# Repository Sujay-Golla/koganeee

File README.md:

# Koganeee 
(JJK Reference) Flying room voice assistant with a screen  

**Demo video:** https://youtu.be/gkjLtGN1tb8

## Inspiration
As a Jujutsu Kaisen fan and an admirer of flying pets, I wanted to make Kogane for my room. The objective of Kogane is to be a person-following flying pet assistant that can communicate with voice and through a retractable screen, sort of like a flying Alexa but friendlier! I also wanted to make drones for a while and it seemed like a cool approach to make Kogane. A use case that I had in mind is when I'm working in my room and my hands are busy and if I need to quickly pull up a tutorial, I would normally have to put things down to find my laptop. Instead with Kogane, I can call for Kogane wherever I am in my room and quickly check for information or pull up a Youtube tutorial from its screen without any physical contact. 

## Challenges
I was new to building FCs and drones, so I had to spend a lot of time getting advice from my friends and revising designs. The timeline was also a bit tight as I had to finish it by Open Sauce. There were a lot of errors on the PCB that I had not anticipated, so I had to make a lot of tweaks with soldering. I also made expensive mistakes with batteries and ESCs but eventually made it work.  

## Technical Features
In terms of the technical features, it is a drone that can be radio controlled, but ready to be implemented with a room-based camera-mmWave sensor fused navigation system for object and person detection, currently displayed in a dashboard for demo. Koganeee also has a mic and LCD screen for the built-in voice assistant with a live Weather app and a Tasks app. It hosts 1303 Brushless motors, a big 1100mAH 4S LiPo battery, and a custom FC with STM32F722RET6 and ESP32-S3-WROOM. Flight computation with accelerometer and ToF sensor is done on-board with the STM32, and is complemented by the ESP32 for data transmission, whether it be directions for autonomous tracking or for cards to be displayed on the screen. 

## Guide to recreating your very own Koganeee!

1. **Start with a revised BOM:** Start off with my [BOM.csv](BOM.csv), check connector compatibility for different modules, and make a good plan for making reliable harnesses
2. **3D Print your Koganeee:** The [CAD folder](cad/) contains the assembly for the shell and drone design, feel free to change the frame type and revise the shell as needed, taking into account some of the notes I added under [CAD notes](cad/README.md) regarding shell assembly, total weight and propeller-clearance.
3. **The flight controller:** Review the [PCB notes](pcb/README.md) and make adjustments to the PCB before ordering it, it's definitely also possible to make it more compact with smaller connectors and better planning, so plan for space optimization!
4. **Set up the firmware.** Follow the [firmware guide](firmware/README.md) for the toolchains and setup order, most of the details for the firmware setup as well as the firmware files are already available and can easily be modified! 
5. **Test in stages:** The [demo guides](firmware/Demo/INDEX.md) cover voice commands, the LCD, microphone, weather, tasks and room mapping, so check those out and ask your favorite AI (I prefer Sol or Gemini) for any clarifications
6. **Go through tests for a safe flight:** Follow the [flight preparation guide](firmware/Demo/FIRST_FLIGHT_PLAN.md), verifying the orientation, radio control and failsafe with propellers off, and as well as the physical connections, especially harnesses and soldered joints

## Build

## CAD Model
### Kogane

### Internal Drone

## PCB
### Fabricated PCB

### Schematic

### PCB Design

### 3D Model

## BOM

| Item | Qty | Price (USD) | Link | Notes |
|------|-----|-------------|------|-------|
| 1303 5500KV brushless motor | 4 | $67.61 | [Rotor Village](https://rotorvillage.ca/geprc-speedx2-1303-5-5500kv-motor/) | |
| 3-inch Gemfan 3018 2-Blade Propeller (4 pairs) | 1 | $3.94 | [AliExpress](https://www.aliexpress.com/item/1005007476443932.html) | |
| 4-in-1 ESC 45A 20x20 | 1 | $30.55 | [AliExpress](https://www.aliexpress.com/item/1005009278492069.html) | |
| GNB 1100mAh 4S 120C HV LiPo XT60 | 1 | $19.72 | [Rotor Village](https://rotorvillage.ca/gnb-1100mah-4s-120c-hv-lipo-xt60/) | |
| Battery strap | 1 | $3.88 | [AliExpress](https://www.aliexpress.com/item/4001316238579.html) | |
| Custom Kogane FC PCB | 2 | $168.84 | [JLCPCB](https://jlcpcb.com) | Design submitted but revisions noted under in the PCB directory (min 2 assembled PCBs) |
| ESP32-S3-WROOM-1-N16R8 | 1 | $15.79 | [AliExpress](https://www.aliexpress.com/item/1005012502278371.html) | Manual solder |
| VL53L1X ToF sensor | 1 | $4.83 | [AliExpress](https://www.aliexpress.com/item/1005007324288727.html) | Manual solder |
| 8GB microSD card | 1 | $3.49 | [AliExpress](https://www.aliexpress.com/item/1005010323860143.html) | FAT32 for iNAV blackbox |
| OV2640 FPC camera module 75MM-160 650nm | 1 | $9.19 | [AliExpress](https://www.aliexpress.com/item/1005003040149873.html) | |
| ILI9341 2.8 inch SPI touch display | 1 | $5.69 | [AliExpress](https://www.aliexpress.com/item/1005006315533240.html) | |
| INMP441 I2S microphone | 1 | $1.59 | [AliExpress](https://www.aliexpress.com/item/1005009213592784.html) | |
| 4 ohm 3W speaker | 1 | $2.46 | [AliExpress](https://www.aliexpress.com/item/1005008626624201.html) | |
| MG90S micro servo | 0 | $0.00 | | Already owned |
| HLK-LD2450 mmWave module | 1 | $6.69 | [AliExpress](https://www.aliexpress.com/item/1005010228798692.html) | |
| USB-UART adapter 3.3V logic | 1 | $1.77 | [AliExpress](https://www.aliexpress.com/item/1005006445462581.html) | Powers LD2450 from laptop USB |
| USB webcam 720p or 1080p | 2 | $7.95 | [AliExpress](https://www.aliexpress.com/item/1005007740023631.html) | Fixed position to laptop USB |
| 4S LiPo charger with AC plug | 1 | $15.00 | [Amazon](https://www.amazon.ca/dp/B0B3Y3JGDG) | |
| XT60 Pigtail Male | 1 | $1.48 | [AliExpress](https://www.aliexpress.com/item/1005009156026988.html) | |
| Radio TX module | 1 | $4.23 | [AliExpress](https://www.aliexpress.com/item/1005010228737836.html) | For future integration as RC transmitter is currently out of budget |
| JST Connector kit | 1 | $6.09 | [AliExpress](https://www.aliexpress.com/item/1005010491522001.html) | |
| M2 nylon standoff kit | 1 | $3.68 | [AliExpress](https://www.aliexpress.com/item/32862529967.html) | |
| Filament (PLA for shell and PETG GF for drone frame) | 2 | $28.68 | [Amazon](https://a.co/d/04z5qBoh) [Amazon](https://a.co/d/00EyYI3x) | doesn't require that much filament, so smaller spools is okay! |
| Connectors, adapters, USB extensions | Depends | < $30 | AliExpress | |
| Radiomaster Pocket | 1 | $96.51 | [Amazon](https://www.amazon.ca/Radiomaster-Transmitter-Portable-Charcoal-transmitter/dp/B0GWPZ96C5?source=ps-sl-shoppingads-lpcontext&th=1) | Or borrow from a friend like I did for testing |

**Total cost (upper bound): $539.66**

## Credits
https://macondo.hackclub.com/docs/flight-controller#stm32cubemx - Very useful guide :D
Thanks to Surya and Alvik for all their guidance with the PCB, drone design, and throughout the build!
Used ChatGPT and various Claude models throughout the design and build process. Only used them for documentation for draft and format generation, I've looked through and edited all of them to keep them consistent with my understanding of the project, so that it is more readable for other people trying to recreate it.

## Next Steps
While all the firmware is available, I didn't have time to install and calibrate cameras for full autonomy. Also didn't have time to design a proper mechanism for screen retraction but that could a simple pulley driven by one servo.

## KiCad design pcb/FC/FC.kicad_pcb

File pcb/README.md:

# PCB notes

The flight-controller source is in [FC/](FC/). The physical prototypes include hand repairs that are absent from these files.

## Fixes for the next revision

| Issue | Fix |
| --- | --- |
| R22 pulls ESP32 IO0 down and SW3 drives it high. | Add a 10 kΩ pull-up and a BOOT button to GND. The original circuit required SW3 for normal boot. The working prototype was repaired. |
| ESP32 EN floats and is connected to STM32 PB4. | Add a dedicated pull-up and reset timing. Design any STM32 reset control explicitly. |
| ESP32 native USB is not routed. | Route GPIO19/20 to a connector with ESD protection. |
| U11 speaker amplifier has SD_MODE tied to GND. | Correct the enable and channel-selection circuit. Do not connect the grounded pin directly to 3.3 V. |
| Battery ADC PC0 is unconnected. | Add a scaled, filtered divider and an accessible test point. |
| F1 is specified for 16 V and Q2 can exceed its ±8 V VGS rating. | Review the power path for full 4S/LiHV voltage, transients and USB backfeeding. |
| Connectors do not match some purchased modules. | Choose exact mating parts, label pin 1 and add strain relief and repair access. |
| LCD and camera reset share the STM32 reset net. LCD MISO is absent. | Add independent peripheral reset and route readback if required. |
| Some labels and firmware assumptions are stale. | Reconcile I2S directions, UARTs, the 25 MHz clock and motor timer/DMA assignments. Reserve the N16R8 memory pins. |

## Before ordering

- Reconcile BOM values and supplier IDs with the chosen components.
- Regenerate ERC and DRC. The saved report is historical.
- Verify the complete ESC harness pinout and every connector's orientation.
- Add test points for supply rails, reset, boot, UART and ADC signals.
- Check power selection and intended loads on the assembled revision.

Details are in the [firmware guide](../firmware/README.md), [pin map](../firmware/companion-esp32s3/PINMAP.md), [power review](../firmware/fc-inav/POWER_REVIEW.md) and [battery-sensing notes](../firmware/fc-inav/BATTERY_SENSE_CHECK.md).

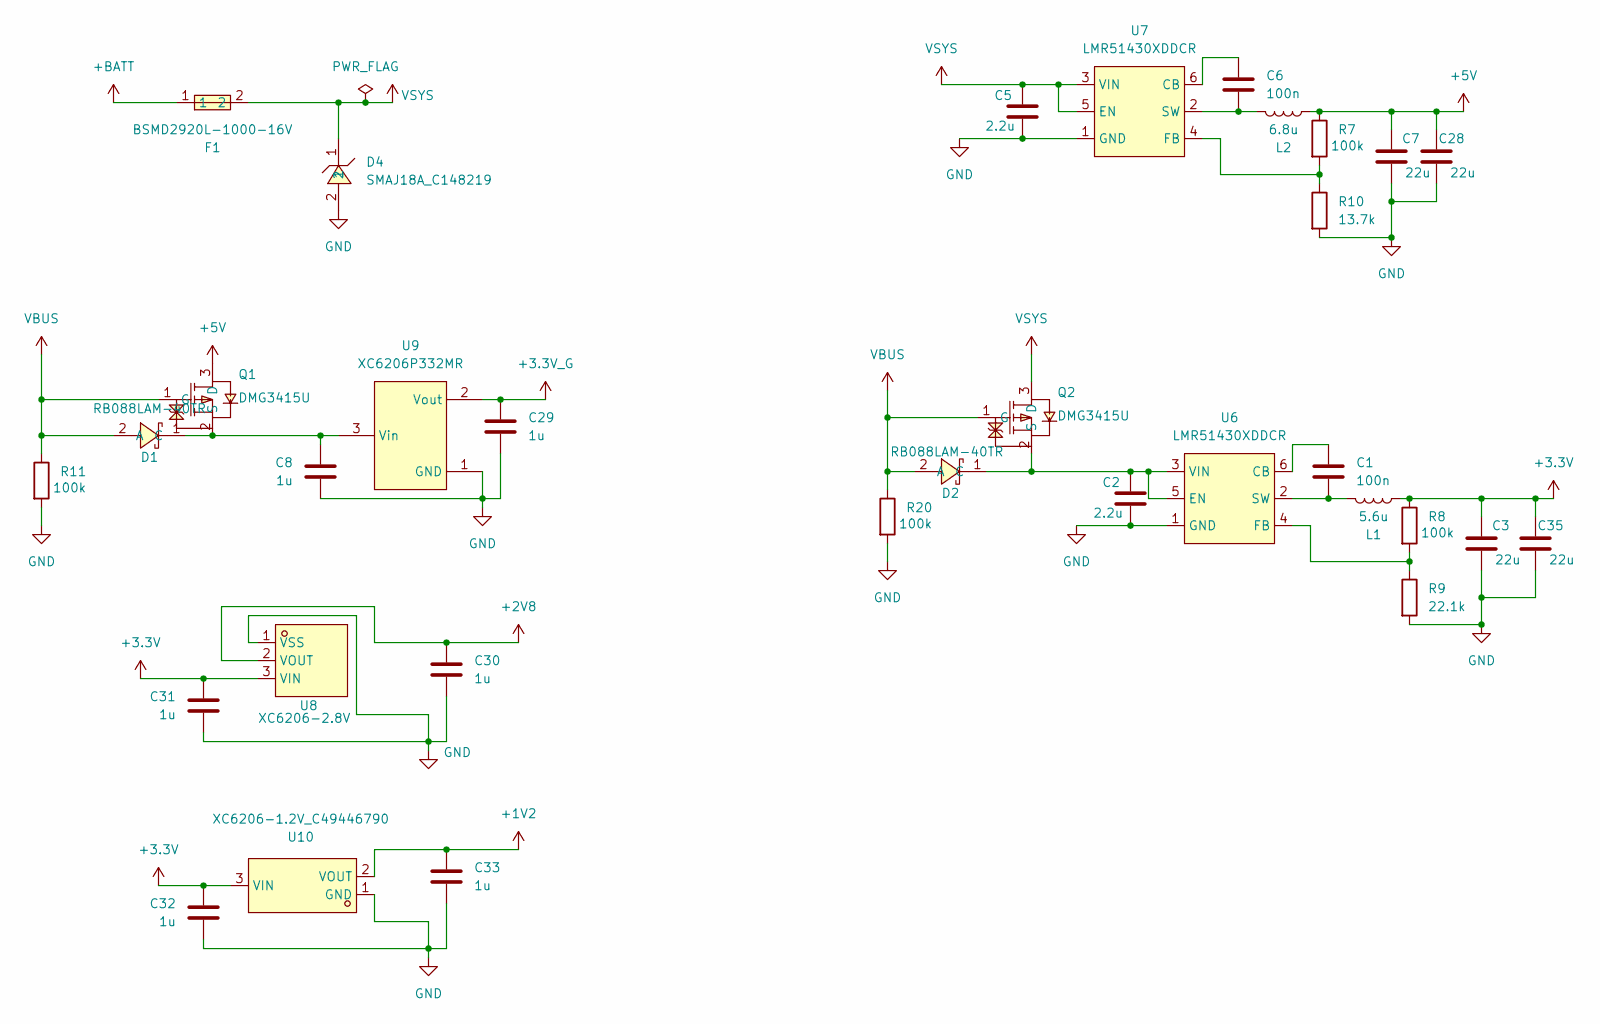
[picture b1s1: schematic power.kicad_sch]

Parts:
C1, C6: 100n; C0603
C2, C5: 2.2u; C0603
C3, C7, C28, C35: 22u; C0805
C8, C29, C30, C31, C32, C33: 1u; C0603
D1, D2: RB088LAM-40TR; SOD-128_L3.7-W2.5-LS4.7-RD; MPN RB088LAM-40TR; LCSC Part C3758383
D4: SMAJ18A_C148219; SMA_L4.4-W2.6-LS5.0-RD; MPN SMAJ18A; LCSC Part C148219
F1: BSMD2920L-1000-16V; F2920; MPN BSMD2920L-1000-16V; LCSC Part C46597958
L1: 5.6u; IND-SMD_L7.0-W6.6_APH0630
L2: 6.8u; IND-SMD_L7.1-W6.6
Q1, Q2: DMG3415U; SOT-23-3_L2.9-W1.3-P1.90-LS2.4-BR-1; MPN DMG3415U; LCSC Part C7202986
R7: 100k; R0603
R8, R11, R20: 100k; R0402
R9: 22.1k; R0402
R10: 13.7k; R0603
U6, U7: LMR51430XDDCR; SOT-23-6_L2.9-W1.6-P0.95-LS2.8-BL; MPN LMR51430XDDCR; LCSC Part C5185863
U8: XC6206-2.8V; SOT-23-3_L2.9-W1.6-P1.90-LS2.8-BR; MPN XC6206-2.8V; LCSC Part C2892669
U9: XC6206P332MR; SOT-23-3_L2.9-W1.6-P1.90-LS2.8-BR; MPN XC6206P332MR-G; LCSC Part C5446
U10: XC6206-1.2V_C49446790; SOT-23-3_L3.0-W1.6-P1.90-LS2.8-BR; MPN XC6206-1.2V; LCSC Part C49446790

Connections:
+1V2: C33.1, U10.2 (VOUT); also elsewhere on the board
+2V8: C30.1, U8.2 (VOUT); also elsewhere on the board
+3.3V: C3.1, C31.1, C32.1, C35.1, L1.2, R8.1, U8.3 (VIN), U10.3 (VIN); also elsewhere on the board
+3.3V_G: C29.1, U9.2 (Vout); also elsewhere on the board
+5V: C7.1, C28.1, L2.2, Q1.3 (D), R7.1; also elsewhere on the board
+BATT: F1.1; also elsewhere on the board
GND: C2.2, C3.2, C5.2, C7.2, C8.2, C28.2, C29.2, C30.2, C31.2, C32.2, C33.2, C35.2, D4.2, R9.2, R10.2, R11.2, R20.2, U6.1 (GND), U7.1 (GND), U8.1 (VSS), U9.1 (GND), U10.1 (GND); also elsewhere on the board
unnamed: C8.1, D1.1 (C), Q1.2 (S), U9.3 (Vin)
unnamed: C2.1, D2.1 (C), Q2.2 (S), U6.3 (VIN), U6.5 (EN)
unnamed: C1.1, U6.6 (CB)
unnamed: R8.2, R9.1, U6.4 (FB)
unnamed: C1.2, L1.1, U6.2 (SW)
unnamed: C6.1, U7.6 (CB)
unnamed: R7.2, R10.1, U7.4 (FB)
unnamed: C6.2, L2.1, U7.2 (SW)
VBUS: D1.2 (A), D2.2 (A), Q1.1 (G), Q2.1 (G), R11.1, R20.1; also elsewhere on the board
VSYS: C5.1, D4.1, F1.2, Q2.3 (D), U7.3 (VIN), U7.5 (EN)

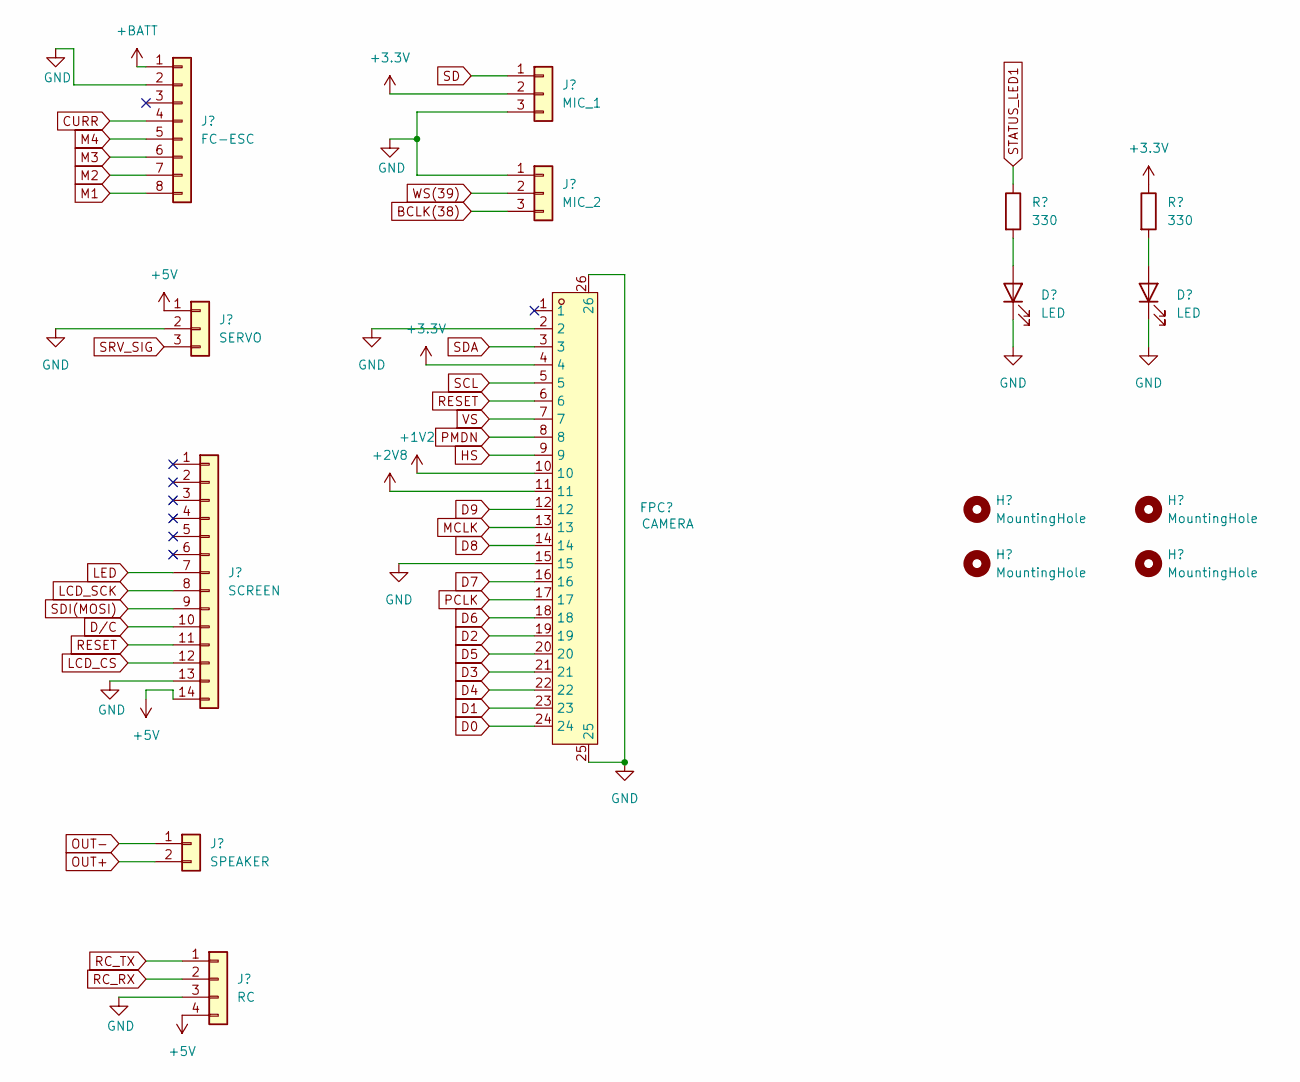
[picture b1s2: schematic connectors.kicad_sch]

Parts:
D3, D5: LED; LED0603-FD
FPC1: CAMERA; FPC-SMD_0510-GX-24PWB-GF-RB; MPN 0510-GX-24PWB-GF-RB; LCSC Part C52722656
H1, H2, H3, H4: MountingHole; MountingHole_2.2mm_M2_Pad_Via
J1: FC-ESC; JST_XH_B8B-XH-AM_1x08_P2.50mm_Vertical
J2: MIC_1; JST_XH_B3B-XH-A_1x03_P2.50mm_Vertical
J3: MIC_2; JST_XH_B3B-XH-A_1x03_P2.50mm_Vertical
J4: SCREEN; JST_XH_B14B-XH-A_1x14_P2.50mm_Vertical
J5: SERVO; JST_XH_B3B-XH-A_1x03_P2.50mm_Vertical
J6: SPEAKER; JST_XH_B2B-XH-A_1x02_P2.50mm_Vertical
J7: RC; JST_XH_B4B-XH-A_1x04_P2.50mm_Vertical
R19, R21: 330; R0603

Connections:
+1V2: FPC1.10; also elsewhere on the board
+2V8: FPC1.11; also elsewhere on the board
+3.3V: FPC1.4, J2.2, R21.1; also elsewhere on the board
+5V: J4.14, J5.1, J7.4; also elsewhere on the board
+BATT: J1.1; also elsewhere on the board
BCLK(38): J3.3; also elsewhere on the board
CURR: J1.4; also elsewhere on the board
D0: FPC1.24; also elsewhere on the board
D1: FPC1.23; also elsewhere on the board
D2: FPC1.19; also elsewhere on the board
D3: FPC1.21; also elsewhere on the board
D4: FPC1.22; also elsewhere on the board
D5: FPC1.20; also elsewhere on the board
D6: FPC1.18; also elsewhere on the board
D7: FPC1.16; also elsewhere on the board
D8: FPC1.14; also elsewhere on the board
D9: FPC1.12; also elsewhere on the board
D/C: J4.10; also elsewhere on the board
GND: D3.1 (K), D5.1 (K), FPC1.2, FPC1.15, FPC1.25, FPC1.26, J1.2, J2.3, J3.1, J4.13, J5.2, J7.3; also elsewhere on the board
HS: FPC1.9; also elsewhere on the board
LCD_CS: J4.12; also elsewhere on the board
LCD_SCK: J4.8; also elsewhere on the board
LED: J4.7; also elsewhere on the board
M1: J1.8; also elsewhere on the board
M2: J1.7; also elsewhere on the board
M3: J1.6; also elsewhere on the board
M4: J1.5; also elsewhere on the board
MCLK: FPC1.13; also elsewhere on the board
unnamed: D3.2 (A), R19.2
unnamed: D5.2 (A), R21.2
OUT+: J6.2; also elsewhere on the board
OUT-: J6.1; also elsewhere on the board
PCLK: FPC1.17; also elsewhere on the board
PMDN: FPC1.8; also elsewhere on the board
RC_RX: J7.2; also elsewhere on the board
RC_TX: J7.1; also elsewhere on the board
RESET: FPC1.6, J4.11; also elsewhere on the board
SCL: FPC1.5; also elsewhere on the board
SD: J2.1; also elsewhere on the board
SDA: FPC1.3; also elsewhere on the board
SDI(MOSI): J4.9; also elsewhere on the board
SRV_SIG: J5.3; also elsewhere on the board
STATUS_LED1: R19.1; also elsewhere on the board
VS: FPC1.7; also elsewhere on the board
WS(39): J3.2; also elsewhere on the board

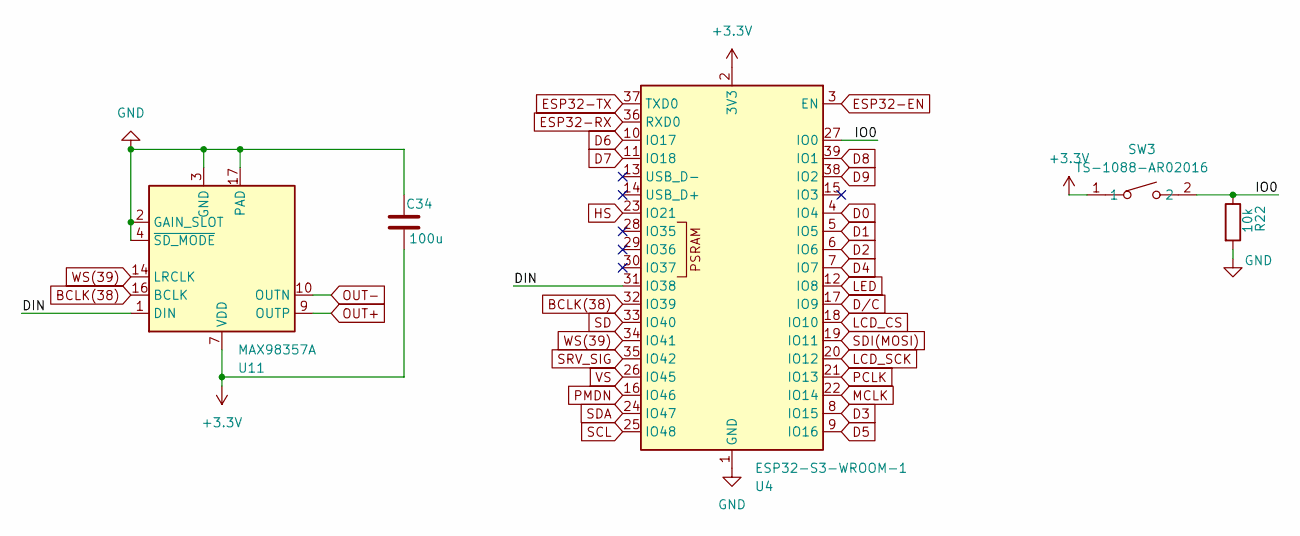
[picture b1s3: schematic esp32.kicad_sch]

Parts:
C34: 100u; C1210
R22: 10k; R0603
SW3: TS-1088-AR02016; SW-SMD_L3.9-W3.0-P4.45; MPN TS-1088-AR02016; LCSC Part C720477
U4: ESP32-S3-WROOM-1
U11: MAX98357A; TQFN-16-1EP_3x3mm_P0.5mm_EP1.23x1.23mm

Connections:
+3.3V: C34.2, SW3.1, U4.2 (3V3), U11.7 (VDD), U11.8 (VDD); also elsewhere on the board
/ESP32/DIN: U4.31 (IO38), U11.1 (DIN)
/ESP32/IO0: R22.1, SW3.2, U4.27 (IO0)
BCLK(38): U4.32 (IO39), U11.16 (BCLK); also elsewhere on the board
D0: U4.4 (IO4); also elsewhere on the board
D1: U4.5 (IO5); also elsewhere on the board
D2: U4.6 (IO6); also elsewhere on the board
D3: U4.8 (IO15); also elsewhere on the board
D4: U4.7 (IO7); also elsewhere on the board
D5: U4.9 (IO16); also elsewhere on the board
D6: U4.10 (IO17); also elsewhere on the board
D7: U4.11 (IO18); also elsewhere on the board
D8: U4.39 (IO1); also elsewhere on the board
D9: U4.38 (IO2); also elsewhere on the board
D/C: U4.17 (IO9); also elsewhere on the board
ESP32-EN: U4.3 (EN); also elsewhere on the board
ESP32-RX: U4.36 (RXD0); also elsewhere on the board
ESP32-TX: U4.37 (TXD0); also elsewhere on the board
GND: C34.1, R22.2, U4.1 (GND), U4.40 (GND), U4.41 (GND), U11.2 (GAIN_SLOT), U11.3 (GND), U11.4 (~SD_MODE), U11.11 (GND), U11.15 (GND), U11.17 (PAD); also elsewhere on the board
HS: U4.23 (IO21); also elsewhere on the board
LCD_CS: U4.18 (IO10); also elsewhere on the board
LCD_SCK: U4.20 (IO12); also elsewhere on the board
LED: U4.12 (IO8); also elsewhere on the board
MCLK: U4.22 (IO14); also elsewhere on the board
OUT+: U11.9 (OUTP); also elsewhere on the board
OUT-: U11.10 (OUTN); also elsewhere on the board
PCLK: U4.21 (IO13); also elsewhere on the board
PMDN: U4.16 (IO46); also elsewhere on the board
SCL: U4.25 (IO48); also elsewhere on the board
SD: U4.33 (IO40); also elsewhere on the board
SDA: U4.24 (IO47); also elsewhere on the board
SDI(MOSI): U4.19 (IO11); also elsewhere on the board
SRV_SIG: U4.35 (IO42); also elsewhere on the board
VS: U4.26 (IO45); also elsewhere on the board
WS(39): U4.34 (IO41), U11.14 (LRCLK); also elsewhere on the board

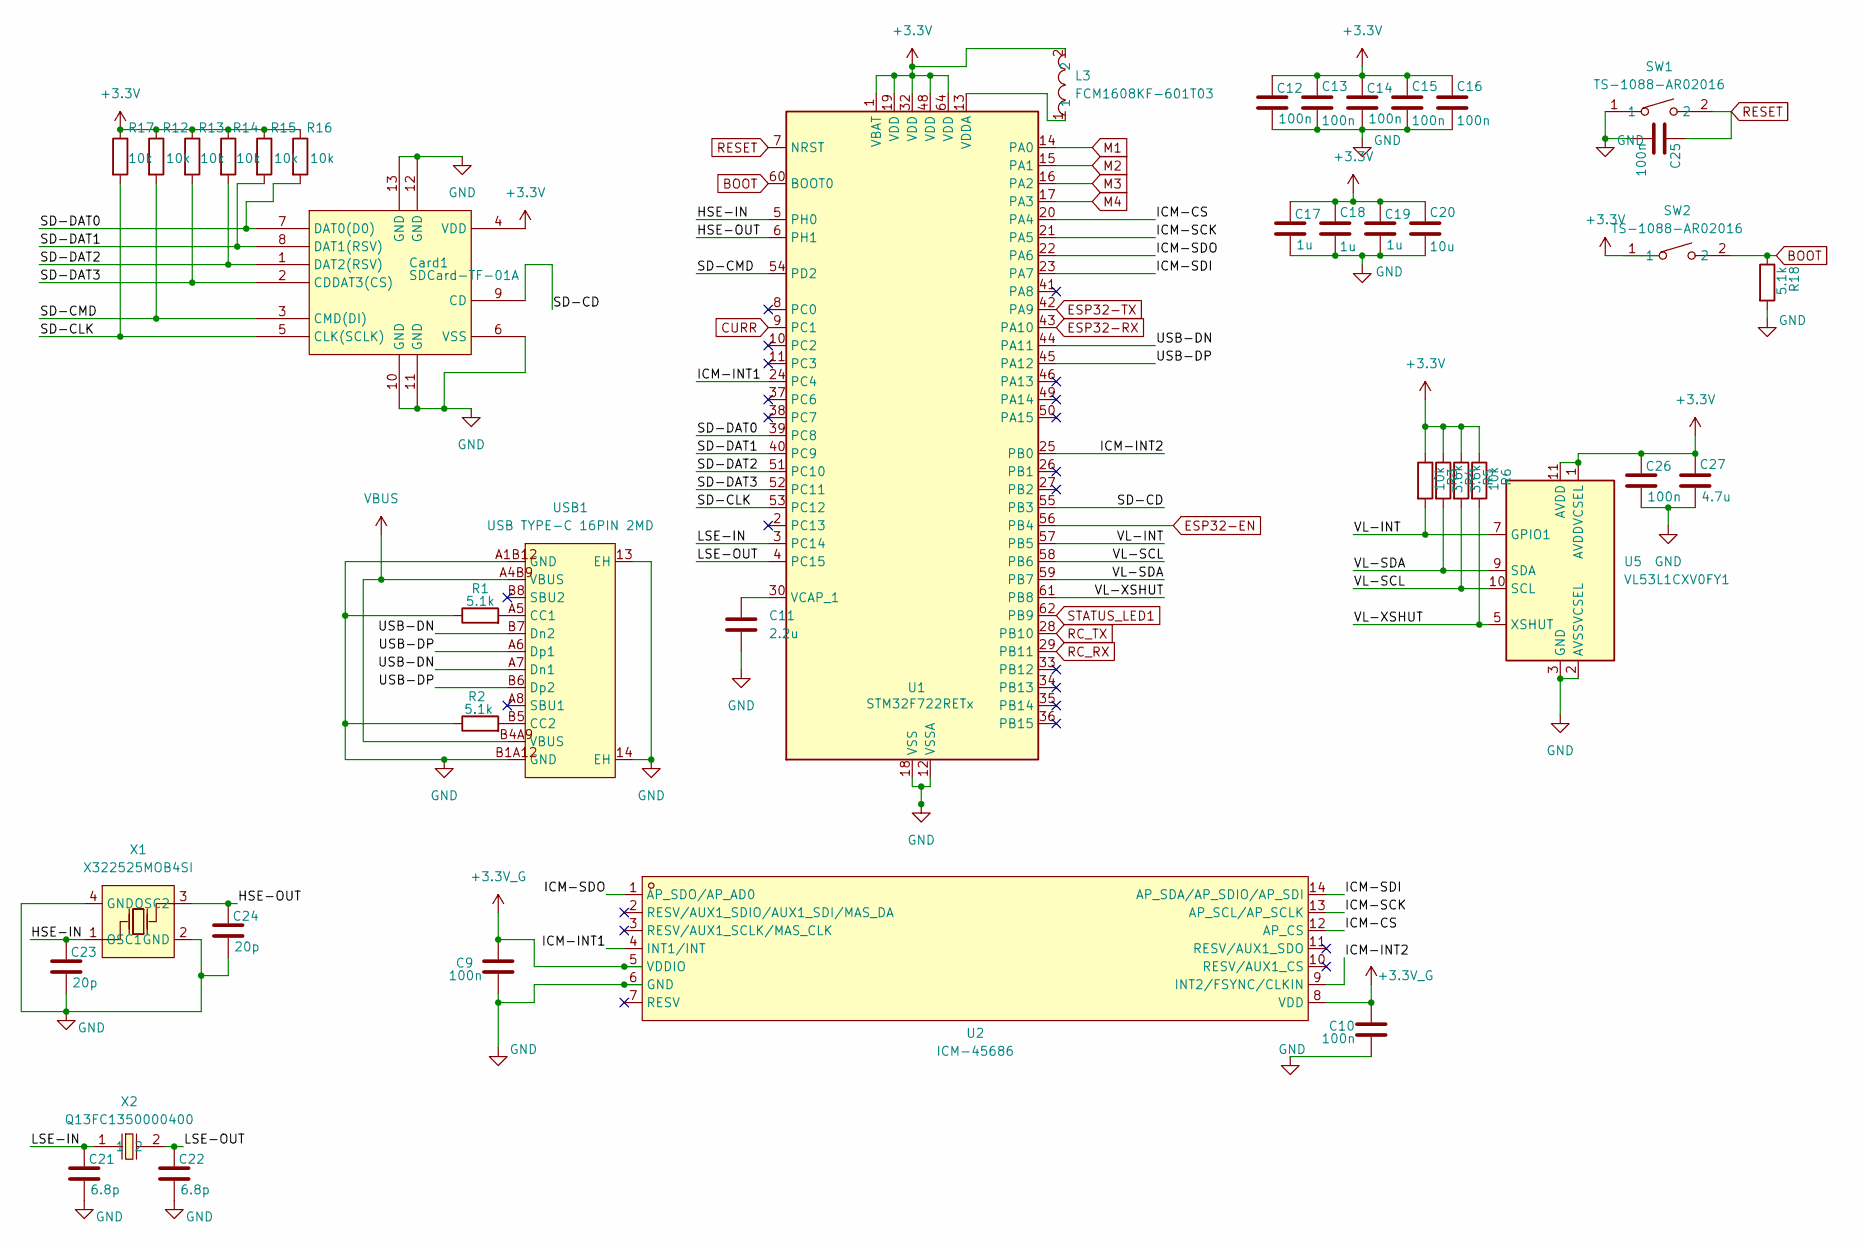
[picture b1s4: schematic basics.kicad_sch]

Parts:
C9, C10, C12, C13, C14, C15, C16, C25, C26: 100n; C0603
C11: 2.2u; C0603
C17, C18, C19: 1u; C0603
C20: 10u; C0603
C21, C22: 6.8p; C0603
C23, C24: 20p; C0603
C27: 4.7u; C0603
Card1: SDCard-TF-01A; TF-SMD_TF-01A; MPN TF-01A; LCSC Part C91145
L3: FCM1608KF-601T03; L0603; MPN FCM1608KF-601T03; LCSC Part C141723
R1, R2, R18: 5.1k; R0603
R3, R6, R12, R13, R14, R15, R16, R17: 10k; R0603
R4, R5: 3.6k; R0603
SW1, SW2: TS-1088-AR02016; SW-SMD_L3.9-W3.0-P4.45; MPN TS-1088-AR02016; LCSC Part C720477
U1: STM32F722RETx; LQFP-64_10x10mm_P0.5mm
U2: ICM-45686; LGA-14_L3.0-W2.5-P0.50-TL; MPN ICM-45686; LCSC Part C22459454
U5: VL53L1CXV0FY1; ST_VL53L1x
USB1: USB TYPE-C 16PIN 2MD; USB-C-SMD_TYPE-C-16PIN-2MD-073; MPN TYPE-C 16PIN 2MD(073); LCSC Part C2765186
X1: X322525MOB4SI; CRYSTAL-SMD_4P-L3.2-W2.5-BL; MPN X322525MOB4SI; LCSC Part C9006
X2: Q13FC1350000400; FC-135R_L3.2-W1.5; MPN Q13FC13500004; LCSC Part C32346

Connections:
+3.3V: C12.1, C13.1, C14.1, C15.1, C16.1, C17.1, C18.1, C19.1, C20.1, C26.1, C27.1, Card1.4 (VDD), L3.2, R3.1, R4.1, R5.1, R6.1, R12.1, R13.1, R14.1, R15.1, R16.1, R17.1, SW2.1, U1.1 (VBAT), U1.19 (VDD), U1.32 (VDD), U1.48 (VDD), U1.64 (VDD), U5.1 (AVDDVCSEL), U5.11 (AVDD); also elsewhere on the board
+3.3V_G: C9.1, C10.1, U2.5 (VDDIO), U2.8 (VDD); also elsewhere on the board
/Basics/HSE-IN: C23.1, U1.5 (PH0), X1.1 (OSC1)
/Basics/HSE-OUT: C24.1, U1.6 (PH1), X1.3 (OSC2)
/Basics/ICM-CS: U1.20 (PA4), U2.12 (AP_CS)
/Basics/ICM-INT1: U1.24 (PC4), U2.4 (INT1/INT)
/Basics/ICM-INT2: U1.25 (PB0), U2.9 (INT2/FSYNC/CLKIN)
/Basics/ICM-SCK: U1.21 (PA5), U2.13 (AP_SCL/AP_SCLK)
/Basics/ICM-SDI: U1.23 (PA7), U2.14 (AP_SDA/AP_SDIO/AP_SDI)
/Basics/ICM-SDO: U1.22 (PA6), U2.1 (AP_SDO/AP_AD0)
/Basics/LSE-IN: C21.1, U1.3 (PC14), X2.1
/Basics/LSE-OUT: C22.1, U1.4 (PC15), X2.2
/Basics/SD-CD: Card1.9 (CD), U1.55 (PB3)
/Basics/SD-CLK: Card1.5 (CLK(SCLK)), R17.2, U1.53 (PC12)
/Basics/SD-CMD: Card1.3 (CMD(DI)), R12.2, U1.54 (PD2)
/Basics/SD-DAT0: Card1.7 (DAT0(D0)), R16.2, U1.39 (PC8)
/Basics/SD-DAT1: Card1.8 (DAT1(RSV)), R15.2, U1.40 (PC9)
/Basics/SD-DAT2: Card1.1 (DAT2(RSV)), R14.2, U1.51 (PC10)
/Basics/SD-DAT3: Card1.2 (CDDAT3(CS)), R13.2, U1.52 (PC11)
/Basics/USB-DN: U1.44 (PA11), USB1.A7 (Dn1), USB1.B7 (Dn2)
/Basics/USB-DP: U1.45 (PA12), USB1.A6 (Dp1), USB1.B6 (Dp2)
/Basics/VL-INT: R3.2, U1.57 (PB5), U5.7 (GPIO1)
/Basics/VL-SCL: R5.2, U1.58 (PB6), U5.10 (SCL)
/Basics/VL-SDA: R4.2, U1.59 (PB7), U5.9 (SDA)
/Basics/VL-XSHUT: R6.2, U1.61 (PB8), U5.5 (XSHUT)
BOOT: R18.1, SW2.2, U1.60 (BOOT0)
CURR: U1.9 (PC1); also elsewhere on the board
ESP32-EN: U1.56 (PB4); also elsewhere on the board
ESP32-RX: U1.43 (PA10); also elsewhere on the board
ESP32-TX: U1.42 (PA9); also elsewhere on the board
GND: C9.2, C10.2, C11.2, C12.2, C13.2, C14.2, C15.2, C16.2, C17.2, C18.2, C19.2, C20.2, C21.2, C22.2, C23.2, C24.2, C25.2, C26.2, C27.2, Card1.6 (VSS), Card1.10 (GND), Card1.11 (GND), Card1.12 (GND), Card1.13 (GND), R1.1, R2.1, R18.2, SW1.1, U1.12 (VSSA), U1.18 (VSS), U1.31 (VSS), U1.47 (VSS), U1.63 (VSS), U2.6 (GND), U5.2 (AVSSVCSEL), U5.3 (GND), U5.4 (GND), U5.6 (GND), U5.12 (GND), USB1.13 (EH), USB1.14 (EH), USB1.A1B12 (GND), USB1.B1A12 (GND), X1.2 (GND), X1.4 (GND); also elsewhere on the board
M1: U1.14 (PA0); also elsewhere on the board
M2: U1.15 (PA1); also elsewhere on the board
M3: U1.16 (PA2); also elsewhere on the board
M4: U1.17 (PA3); also elsewhere on the board
unnamed: C11.1, U1.30 (VCAP_1)
unnamed: L3.1, U1.13 (VDDA)
unnamed: R1.2, USB1.A5 (CC1)
unnamed: R2.2, USB1.B5 (CC2)
RC_RX: U1.29 (PB11); also elsewhere on the board
RC_TX: U1.28 (PB10); also elsewhere on the board
RESET: C25.1, SW1.2, U1.7 (NRST); also elsewhere on the board
STATUS_LED1: U1.62 (PB9); also elsewhere on the board
VBUS: USB1.A4B9 (VBUS), USB1.B4A9 (VBUS); also elsewhere on the board

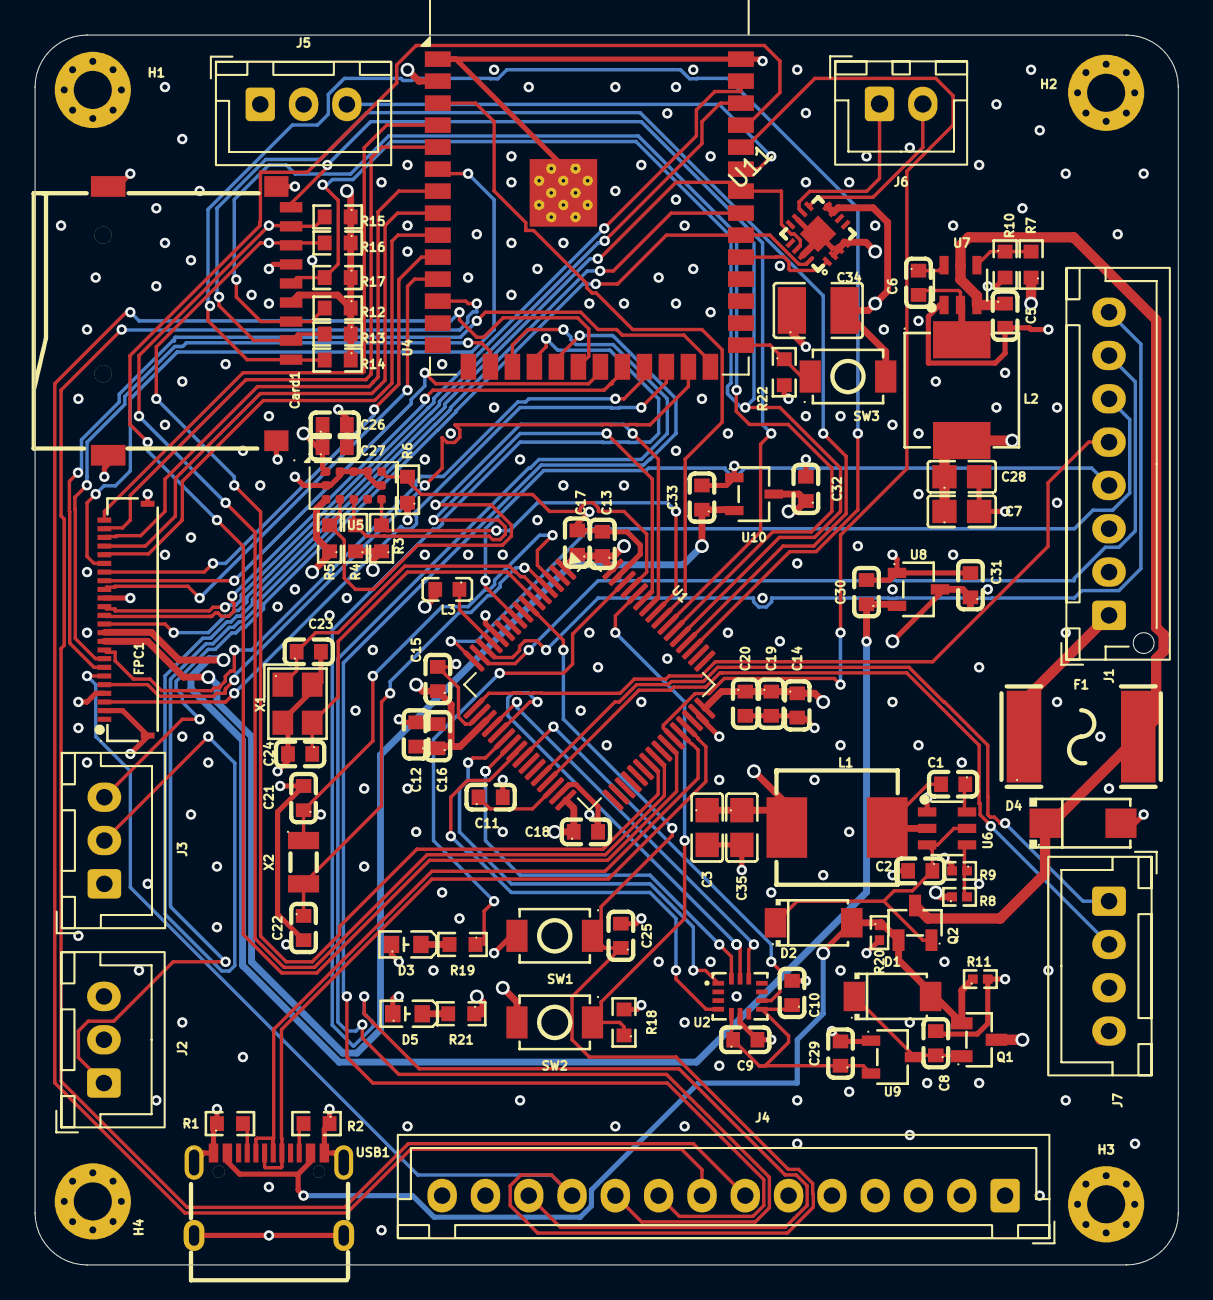
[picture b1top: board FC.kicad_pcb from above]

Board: 4 copper layers, 66.0 x 71.0 mm, 96 parts (0 on the bottom side), 89 nets.

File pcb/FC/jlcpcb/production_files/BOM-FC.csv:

Comment,Designator,Footprint,LCSC,Quantity
100k,R7,R0603,C2933198,1
100k,"R11,R20,R8",R0402,C844504,3
100n,"C1,C10,C12,C13,C14,C15,C16,C25,C26,C6,C9",C0603,C1591,11
100u,C34,C1210,C162511,1
10k,"R12,R13,R14,R15,R16,R17,R22,R3,R6",R0603,C2933198,9
10u,C20,C0603,C1591,1
13.7k,R10,R0603,C2933198,1
1u,"C17,C18,C19,C29,C30,C31,C32,C33,C8",C0603,C1591,9
2.2u,"C11,C2,C5",C0603,C1591,3
20p,"C23,C24",C0603,C1591,2
22.1k,R9,R0402,C844504,1
22u,"C28,C3,C35,C7",C0805,C602037,4
3.6k,"R4,R5",R0603,C2933198,2
330,"R19,R21",R0603,C2933198,2
4.7u,C27,C0603,C1591,1
5.1k,"R1,R18,R2",R0603,C2933198,3
5.6u,L1,IND-SMD_L7.0-W6.6_APH0630,C5349708,1
6.8p,"C21,C22",C0603,C1591,2
6.8u,L2,IND-SMD_L7.1-W6.6,C5349706,1
BSMD2920L-1000-16V,F1,F2920,C46597958,1
CAMERA,FPC1,FPC-SMD_0510-GX-24PWB-GF-RB,C52722656,1
DMG3415U,"Q1,Q2",SOT-23-3_L2.9-W1.3-P1.90-LS2.4-BR-1,C7202986,2
FCM1608KF-601T03,L3,L0603,C141723,1
ICM-45686,U2,LGA-14_L3.0-W2.5-P0.50-TL,C22459454,1
LED,"D3,D5",LED0603-FD,C19171390,2
LMR51430XDDCR,"U6,U7",SOT-23-6_L2.9-W1.6-P0.95-LS2.8-BL,C5185863,2
MAX98357A,U11,TQFN-16_L3.0-W3.0-P0.50-BL-EP1.5,C910544,1
Q13FC1350000400,X2,FC-135R_L3.2-W1.5,C32346,1
RB088LAM-40TR,"D1,D2",SOD-128_L3.7-W2.5-LS4.7-RD,C3758383,2
SDCard-TF-01A,Card1,TF-SMD_TF-01A,C91145,1
SMAJ18A_C148219,D4,SMA_L4.4-W2.6-LS5.0-RD,C148219,1
TS-1088-AR02016,"SW1,SW2,SW3",SW-SMD_L3.9-W3.0-P4.45,C720477,3
USB TYPE-C 16PIN 2MD,USB1,USB-C-SMD_TYPE-C-16PIN-2MD-073,C2765186,1
X322525MOB4SI,X1,CRYSTAL-SMD_4P-L3.2-W2.5-BL,C9006,1
XC6206-1.2V_C49446790,U10,SOT-23-3_L3.0-W1.6-P1.90-LS2.8-BR,C49446790,1
XC6206-2.8V,U8,SOT-23-3_L2.9-W1.6-P1.90-LS2.8-BR,C2892669,1
XC6206P332MR,U9,SOT-23-3_L2.9-W1.6-P1.90-LS2.8-BR,C5446,1
RC,J7,JST_XH_B4B-XH-A_1x04_P2.50mm_Vertical,,1
MIC_2,J3,JST_XH_B3B-XH-A_1x03_P2.50mm_Vertical,,1
MIC_1,J2,JST_XH_B3B-XH-A_1x03_P2.50mm_Vertical,,1
FC-ESC,J1,JST_XH_B8B-XH-AM_1x08_P2.50mm_Vertical,,1
ESP32-S3-WROOM-1,U4,ESP32-S3-WROOM-1,,1
VL53L1CXV0FY1,U5,ST_VL53L1x,,1
STM32F722RETx,U1,LQFP-64_10x10mm_P0.5mm,,1
SCREEN,J4,JST_XH_B14B-XH-A_1x14_P2.50mm_Vertical,,1
SERVO,J5,JST_XH_B3B-XH-A_1x03_P2.50mm_Vertical,,1
SPEAKER,J6,JST_XH_B2B-XH-A_1x02_P2.50mm_Vertical,,1

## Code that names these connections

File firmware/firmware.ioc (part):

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Mcu.Name=STM32F722R(C-E)Tx
Mcu.Package=LQFP64
Mcu.UserName=STM32F722RETx
PA0-WKUP.Signal=S_TIM2_CH1_ETR
PA1.Signal=S_TIM2_CH2
PA10.GPIOParameters=GPIO_Label
PA10.GPIO_Label=ESP32-RX
PA10.Mode=Asynchronous
PA10.Signal=USART1_RX
PA11.Mode=Host_Only
PA11.Signal=USB_OTG_FS_DM
PA12.Mode=Host_Only
PA12.Signal=USB_OTG_FS_DP
PA2.Signal=S_TIM2_CH3
PA3.Signal=S_TIM2_CH4
PA4.GPIOParameters=GPIO_Label
PA4.GPIO_Label=ICM-CS
PA4.Mode=NSS_Signal_Hard_Output
PA4.Signal=SPI1_NSS
PA5.GPIOParameters=GPIO_Label
PA5.GPIO_Label=ICM-SCK
PA5.Mode=Full_Duplex_Master
PA5.Signal=SPI1_SCK
PA6.GPIOParameters=GPIO_Label
PA6.GPIO_Label=ICM-SDO
PA6.Mode=Full_Duplex_Master
PA6.Signal=SPI1_MISO
PA7.GPIOParameters=GPIO_Label
PA7.GPIO_Label=ICM-SDI
PA7.Mode=Full_Duplex_Master
PA7.Signal=SPI1_MOSI
PA9.GPIOParameters=GPIO_Label
PA9.GPIO_Label=ESP32-TX
PA9.Mode=Asynchronous
PA9.Signal=USART1_TX
PB0.GPIOParameters=GPIO_Label
PB0.GPIO_Label=ICM-INT2
PB0.Signal=GPXTI0
PB10.Mode=Asynchronous
PB10.Signal=USART3_TX
PB11.Mode=Asynchronous
PB11.Signal=USART3_RX
PB3.GPIOParameters=GPIO_Label
PB3.GPIO_Label=SD-CD
PB3.Signal=GPIO_Input
PB4.GPIOParameters=PinState,GPIO_PuPd,GPIO_Label,GPIO_ModeDefaultOutputPP
PB4.GPIO_Label=ESP32-EN
PB4.GPIO_ModeDefaultOutputPP=GPIO_MODE_OUTPUT_OD
PB4.GPIO_PuPd=GPIO_NOPULL
PB4.PinState=GPIO_PIN_SET
PB4.Signal=GPIO_Output
PB5.GPIOParameters=GPIO_Label
PB5.GPIO_Label=VL-INT
PB5.Signal=GPXTI5
PB6.GPIOParameters=GPIO_Label
PB6.GPIO_Label=VL-SCL
PB6.Mode=I2C
PB6.Signal=I2C1_SCL
PB7.GPIOParameters=GPIO_Label
PB7.GPIO_Label=VL-SDA
PB7.Mode=I2C
PB7.Signal=I2C1_SDA
PB8.GPIOParameters=GPIO_Label,GPIO_ModeDefaultOutputPP
PB8.GPIO_Label=VL-XSHUT
PB8.GPIO_ModeDefaultOutputPP=GPIO_MODE_OUTPUT_OD
PB8.Signal=GPIO_Output
PB9.GPIOParameters=GPIO_Label
PB9.GPIO_Label=STATUS_LED1
PB9.Signal=GPIO_Output
PC1.Signal=ADCx_IN11
PC10.Mode=SD_4_bits_Wide_bus
PC10.Signal=SDMMC1_D2
PC11.Mode=SD_4_bits_Wide_bus
PC11.Signal=SDMMC1_D3
PC12.Mode=SD_4_bits_Wide_bus
PC12.Signal=SDMMC1_CK
PC14-OSC32_IN.Mode=LSE-External-Oscillator
PC14-OSC32_IN.Signal=RCC_OSC32_IN
PC15-OSC32_OUT.Mode=LSE-External-Oscillator
PC15-OSC32_OUT.Signal=RCC_OSC32_OUT
PC8.Mode=SD_4_bits_Wide_bus
PC8.Signal=SDMMC1_D0
PC9.Mode=SD_4_bits_Wide_bus
PC9.Signal=SDMMC1_D1
PD2.Mode=SD_4_bits_Wide_bus
PD2.Signal=SDMMC1_CMD
PH0-OSC_IN.Mode=HSE-External-Oscillator
PH0-OSC_IN.Signal=RCC_OSC_IN
PH1-OSC_OUT.Mode=HSE-External-Oscillator
PH1-OSC_OUT.Signal=RCC_OSC_OUT
RCC.HSE_VALUE=25000000
board=custom

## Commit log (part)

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2026-06-01 starting BOM and Journal
2026-06-13 Update journal with new entry and total hours
    Updated total hours and added new journal entry for June 8 detailing project progress and changes.
2026-06-13 Update BOM.csv with new items and pricing in CAD
